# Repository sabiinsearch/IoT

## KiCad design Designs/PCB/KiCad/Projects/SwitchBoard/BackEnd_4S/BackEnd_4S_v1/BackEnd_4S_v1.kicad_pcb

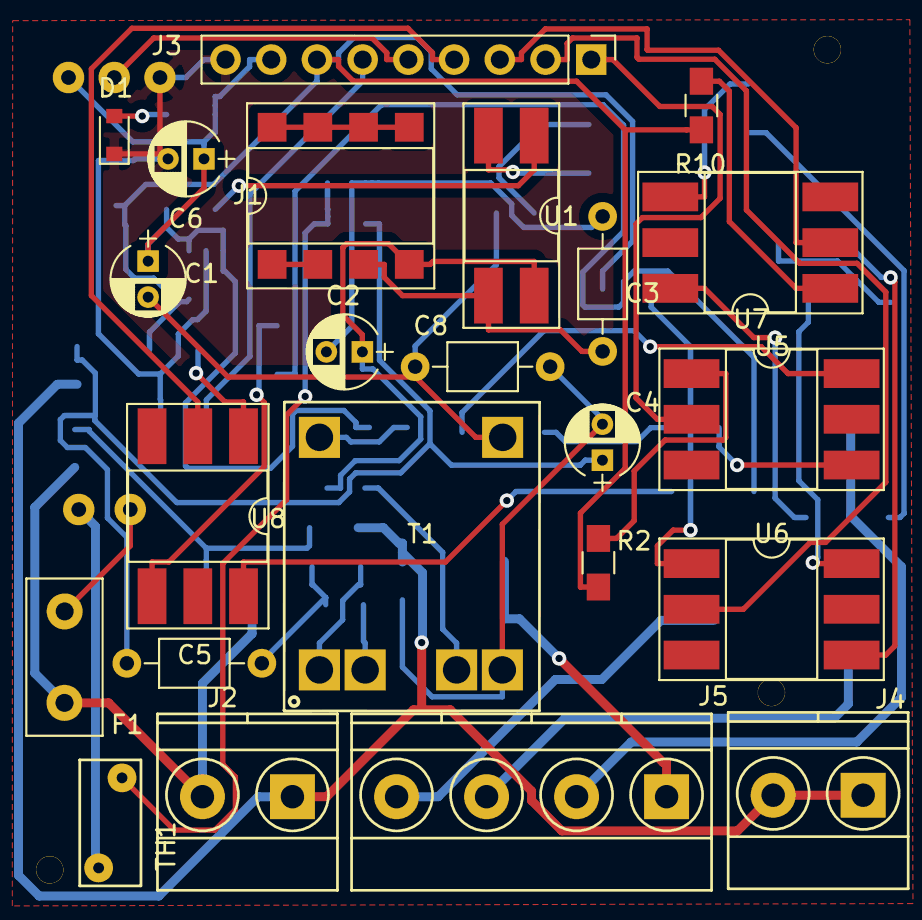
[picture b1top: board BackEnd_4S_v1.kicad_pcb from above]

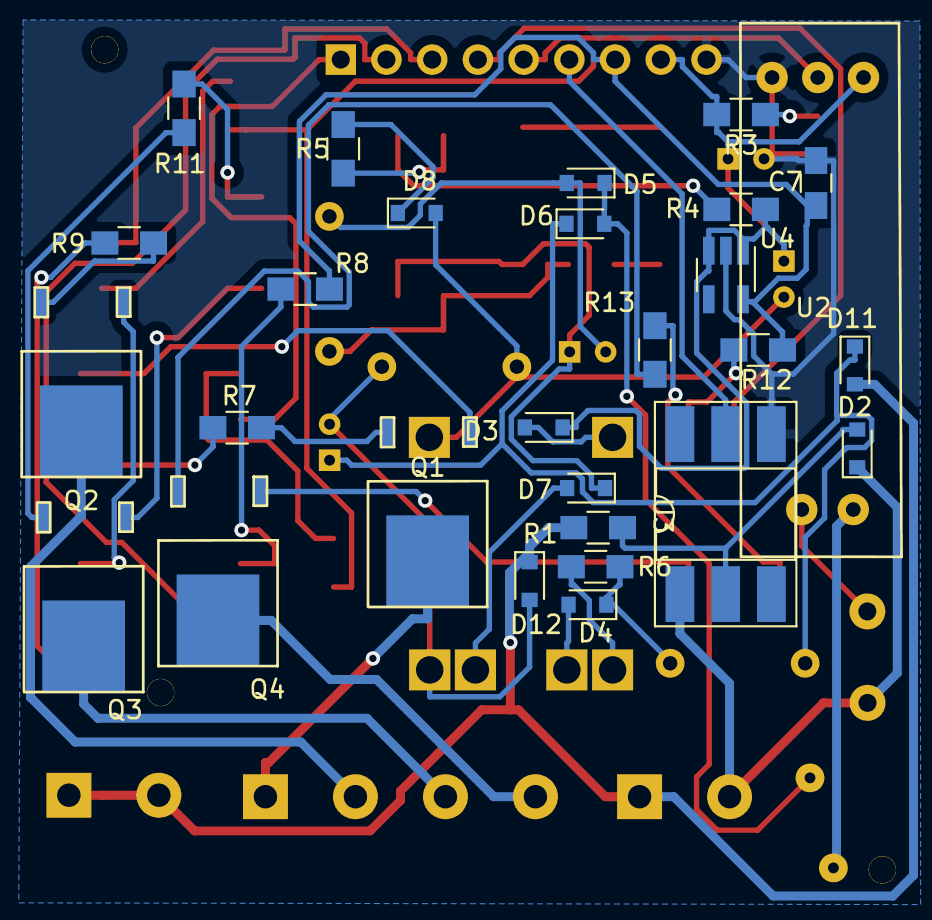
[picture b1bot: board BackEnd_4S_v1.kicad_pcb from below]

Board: 2 copper layers, 54 parts (28 on the bottom side), 52 nets.

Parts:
C1, C4: 4.7uF/400V; CP_Radial_D4.0mm_P2.00mm
C2: 1uF/63V; CP_Radial_D4.0mm_P2.00mm
C3: 47nf; C_Axial_L3.8mm_D2.6mm_P7.50mm_Horizontal
C5, C8: 2A222J / 2.2nF; C_Axial_L3.8mm_D2.6mm_P7.50mm_Horizontal
C6: 470uF/10V; CP_Radial_D4.0mm_P2.00mm
C7: 2.2uf; C_0805_HandSoldering
D1: LED1; D_0805
D2, D7: IN4148; D_0805
D3: SR360; D_0805
D4: FR107; D_0805
D5, D6, D11, D12: IN4007; D_0805
D8: PH C4V3; D_0805
F1: Fuse_Small; Fuse_TE5_Littlefuse-395Series
J1: AP8022; DIP-8_W7.62mm_SMDSocket_SmallPads
J2, J4: Screw_Terminal_01x02; TerminalBlock_Phoenix_MKDS1.5-2pol
J3: Conn_01x09_Female; Pin_Header_Straight_1x09_Pitch2.54mm
J5: Screw_Terminal_01x04; TerminalBlock_Phoenix_MKDS1.5-4pol
M1, M2, M3: MountingHole_1.5mm; MountingHole1.5mm
Q1, Q2, Q3, Q4: BT136-500; BT136S
R1: 220K; R_0805_HandSoldering
R2, R8, R10, R12: 100E; R_0805_HandSoldering
R3: 2.2K; R_0805_HandSoldering
R4, R5: 330 R; R_0805_HandSoldering
R6: 100K; R_0805_HandSoldering
R7, R9, R11, R13: 470E; R_0805_HandSoldering
T1: F12-090; Transformer
TH1: NTC; RV_Disc_D7_W3.4_P5
U1: EL817; DIP-4_W8.89mm_SMDSocket_LongPads
U2: ACS712
U3: 4N35; DIP-6_W8.89mm_SMDSocket_LongPads
U4: AP2112K-3.3; SOT-23-5_HandSoldering
U5, U6, U7, U8: MOC3021; DIP-6_W8.89mm_SMDSocket_LongPads

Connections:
/3.3V: C7.2, J3.7, R2.2, R8.2, R10.2, R12.2, U4.5
/5V: C1.1, C6.1, D3.1, J3.8, R3.2, R4.2, U2.3, U4.1, U4.3
/DSW1: J3.1, U5.2
/DSW2: J3.2, U6.2
/DSW3: J3.3, U7.2
/DSW4: J3.4, U8.2
/Energy_Sensor: J3.5, U2.4
/GND: C6.2, C7.1, D1.1, J3.9, U2.5, U3.4, U4.2
/Mains_Live_In: D2.1, F1.1, J2.2, U3.1
/Mains_Live_Out: TH1.2, U2.1
/Mains_Neutral: D11.2, D12.1, J2.1, J4.1, J4.2, R1.2
/Opto_In: J3.6, U3.5
/Out1: J5.1, Q1.1
/Out2: J5.2, Q2.1
/Out3: J5.3, Q3.1
/Out4: J5.4, Q4.1
unnamed: C1.2, C8.2, D8.2, T1.5
unnamed: C2.1, D7.1, J1.4, U1.4
unnamed: C2.2, C3.1, D5.2
unnamed: C3.2, J1.3, U1.3
unnamed: C4.1, C5.1, D6.1, D11.1
unnamed: C4.2, C8.1, D12.2, T1.4
unnamed: C5.2, D4.1, R6.2
unnamed: D1.2, R3.1
unnamed: D2.2, R1.1, U3.2
unnamed: D3.2, T1.6
unnamed: D4.2, T1.2
unnamed: D5.1, D6.2, TH1.1
unnamed: D7.2, T1.3
unnamed: D8.1, R5.2
unnamed: F1.2, U2.2
unnamed: J1.1, J1.2
unnamed: J1.5, J1.6, J1.7, J1.8
unnamed: Q1.2, U5.6
unnamed: Q1.3, R7.1
unnamed: Q2.2, U6.6
unnamed: Q2.3, R9.1
unnamed: Q3.2, U7.6
unnamed: Q3.3, R11.1
unnamed: Q4.2, U8.6
unnamed: Q4.3, R13.1
unnamed: R2.1, U5.1
unnamed: R4.1, U1.1
unnamed: R5.1, U1.2
unnamed: R6.1, T1.1
unnamed: R7.2, U5.4
unnamed: R8.1, U6.1
unnamed: R9.2, U6.4
unnamed: R10.1, U7.1
unnamed: R11.2, U7.4
unnamed: R12.1, U8.1
unnamed: R13.2, U8.4

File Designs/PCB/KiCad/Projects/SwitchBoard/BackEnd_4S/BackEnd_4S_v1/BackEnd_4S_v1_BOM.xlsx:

Ref | Qnty | Value
C1, C4 | 2 | 4.7uF/400V
C2 | 1 | 1uF/63V
C3 | 1 | 47nf
C5, C8 | 2 | 2A222J / 2.2nF
C6 | 1 | 470uF/10V
C7 | 1 | 2.2uf
D1 | 1 | LED1
D2, D7 | 2 | IN4148
D3 | 1 | SR360
D4 | 1 | FR107
D5, D6, D11, D12 | 4 | IN4007
D8 | 1 | PH C4V3
F1 | 1 | Fuse_Small
J1 | 1 | AP8022
J2, J4 | 2 | Screw_Terminal_01x02
J3 | 1 | Conn_01x09_Female
J5 | 1 | Screw_Terminal_01x04
Q1, Q2, Q3, Q4 | 4 | BT136-500
R1 | 1 | 220K
R2, R8, R10, R12 | 4 | 100E
R3 | 1 | 2.2K
R4, R5 | 2 | 330 R
R6 | 1 | 100K
R7, R9, R11, R13 | 4 | 470E
T1 | 1 | F12-090
TH1 | 1 | NTC
U1 | 1 | EL817
U2 | 1 | ACS712
U3 | 1 | 4N35
U4 | 1 | AP2112K-3.3
U5, U6, U7, U8 | 4 | MOC3021

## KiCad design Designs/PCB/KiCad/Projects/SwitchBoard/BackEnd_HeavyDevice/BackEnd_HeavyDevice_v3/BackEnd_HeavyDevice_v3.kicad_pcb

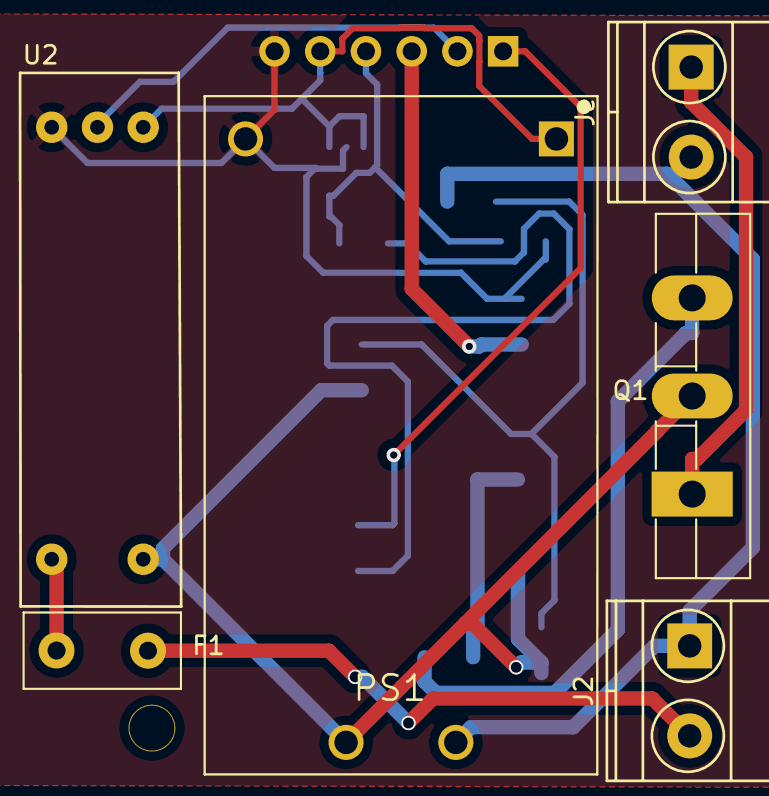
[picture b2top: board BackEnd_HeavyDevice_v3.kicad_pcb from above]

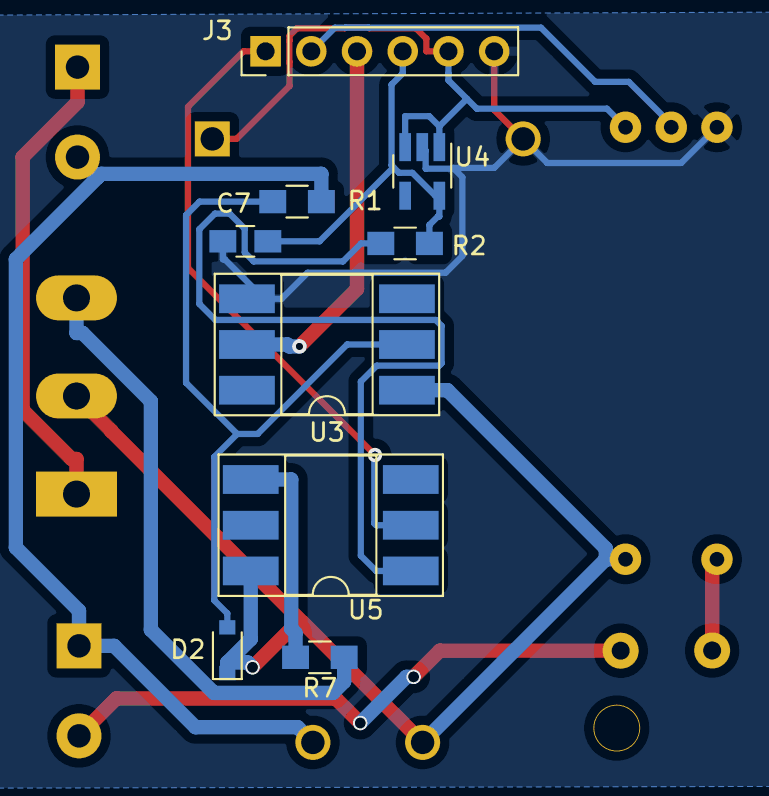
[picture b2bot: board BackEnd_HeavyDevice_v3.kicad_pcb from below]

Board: 2 copper layers, 16 parts (9 on the bottom side), 15 nets.

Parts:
C7: 2.2uf; C_0805_HandSoldering
D2: IN14007; D_0805
F1: Fuse_Small; Fuse_TE5_Littlefuse-395Series
J2: Screw_Terminal_01x02; TerminalBlock_Phoenix_MKDS1.5-2pol
J3: Conn_01x06_Female; PinHeader_1x06_P2.54mm_Vertical
Je: Screw_Terminal_01x02; TerminalBlock_Phoenix_MKDS1.5-2pol
M1: MountingHole_2.1mm; MountingHole_2.5mm
PS1: HLK-PM01; 277
Q1: BT136-500; GN27120BN
R1: 220K; R_0805_HandSoldering
R2: 100E; R_0805_HandSoldering
R7: 470E; R_0805_HandSoldering
U2: ACS712
U3: 4N35; DIP-6_W8.89mm_SMDSocket_LongPads
U4: AP2112K-3.3; SOT-23-5_HandSoldering
U5: MOC3021; DIP-6_W8.89mm_SMDSocket_LongPads

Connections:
/3.3V: C7.2, J3.4, R2.2, U4.5
/5V: J3.5, PS1.5, U2.3, U4.1, U4.3
/DSW1: J3.1, U5.2
/Energy_Sensor: J3.2, U2.4
/GND: C7.1, J3.6, PS1.4, U2.5, U3.4, U4.2
/Mains_Live_In: F1.1, J2.2
/Mains_Live_Out: D2.1, PS1.2, Q1.2, U2.1, U3.1, U5.6
/Mains_Neutral: J2.1, Je.2, PS1.1, R1.2
/Opto_In: J3.3, U3.5
/Out1: Je.1, Q1.1
unnamed: D2.2, R1.1, U3.2
unnamed: F1.2, U2.2
unnamed: Q1.3, R7.1
unnamed: R2.1, U5.1
unnamed: R7.2, U5.4
